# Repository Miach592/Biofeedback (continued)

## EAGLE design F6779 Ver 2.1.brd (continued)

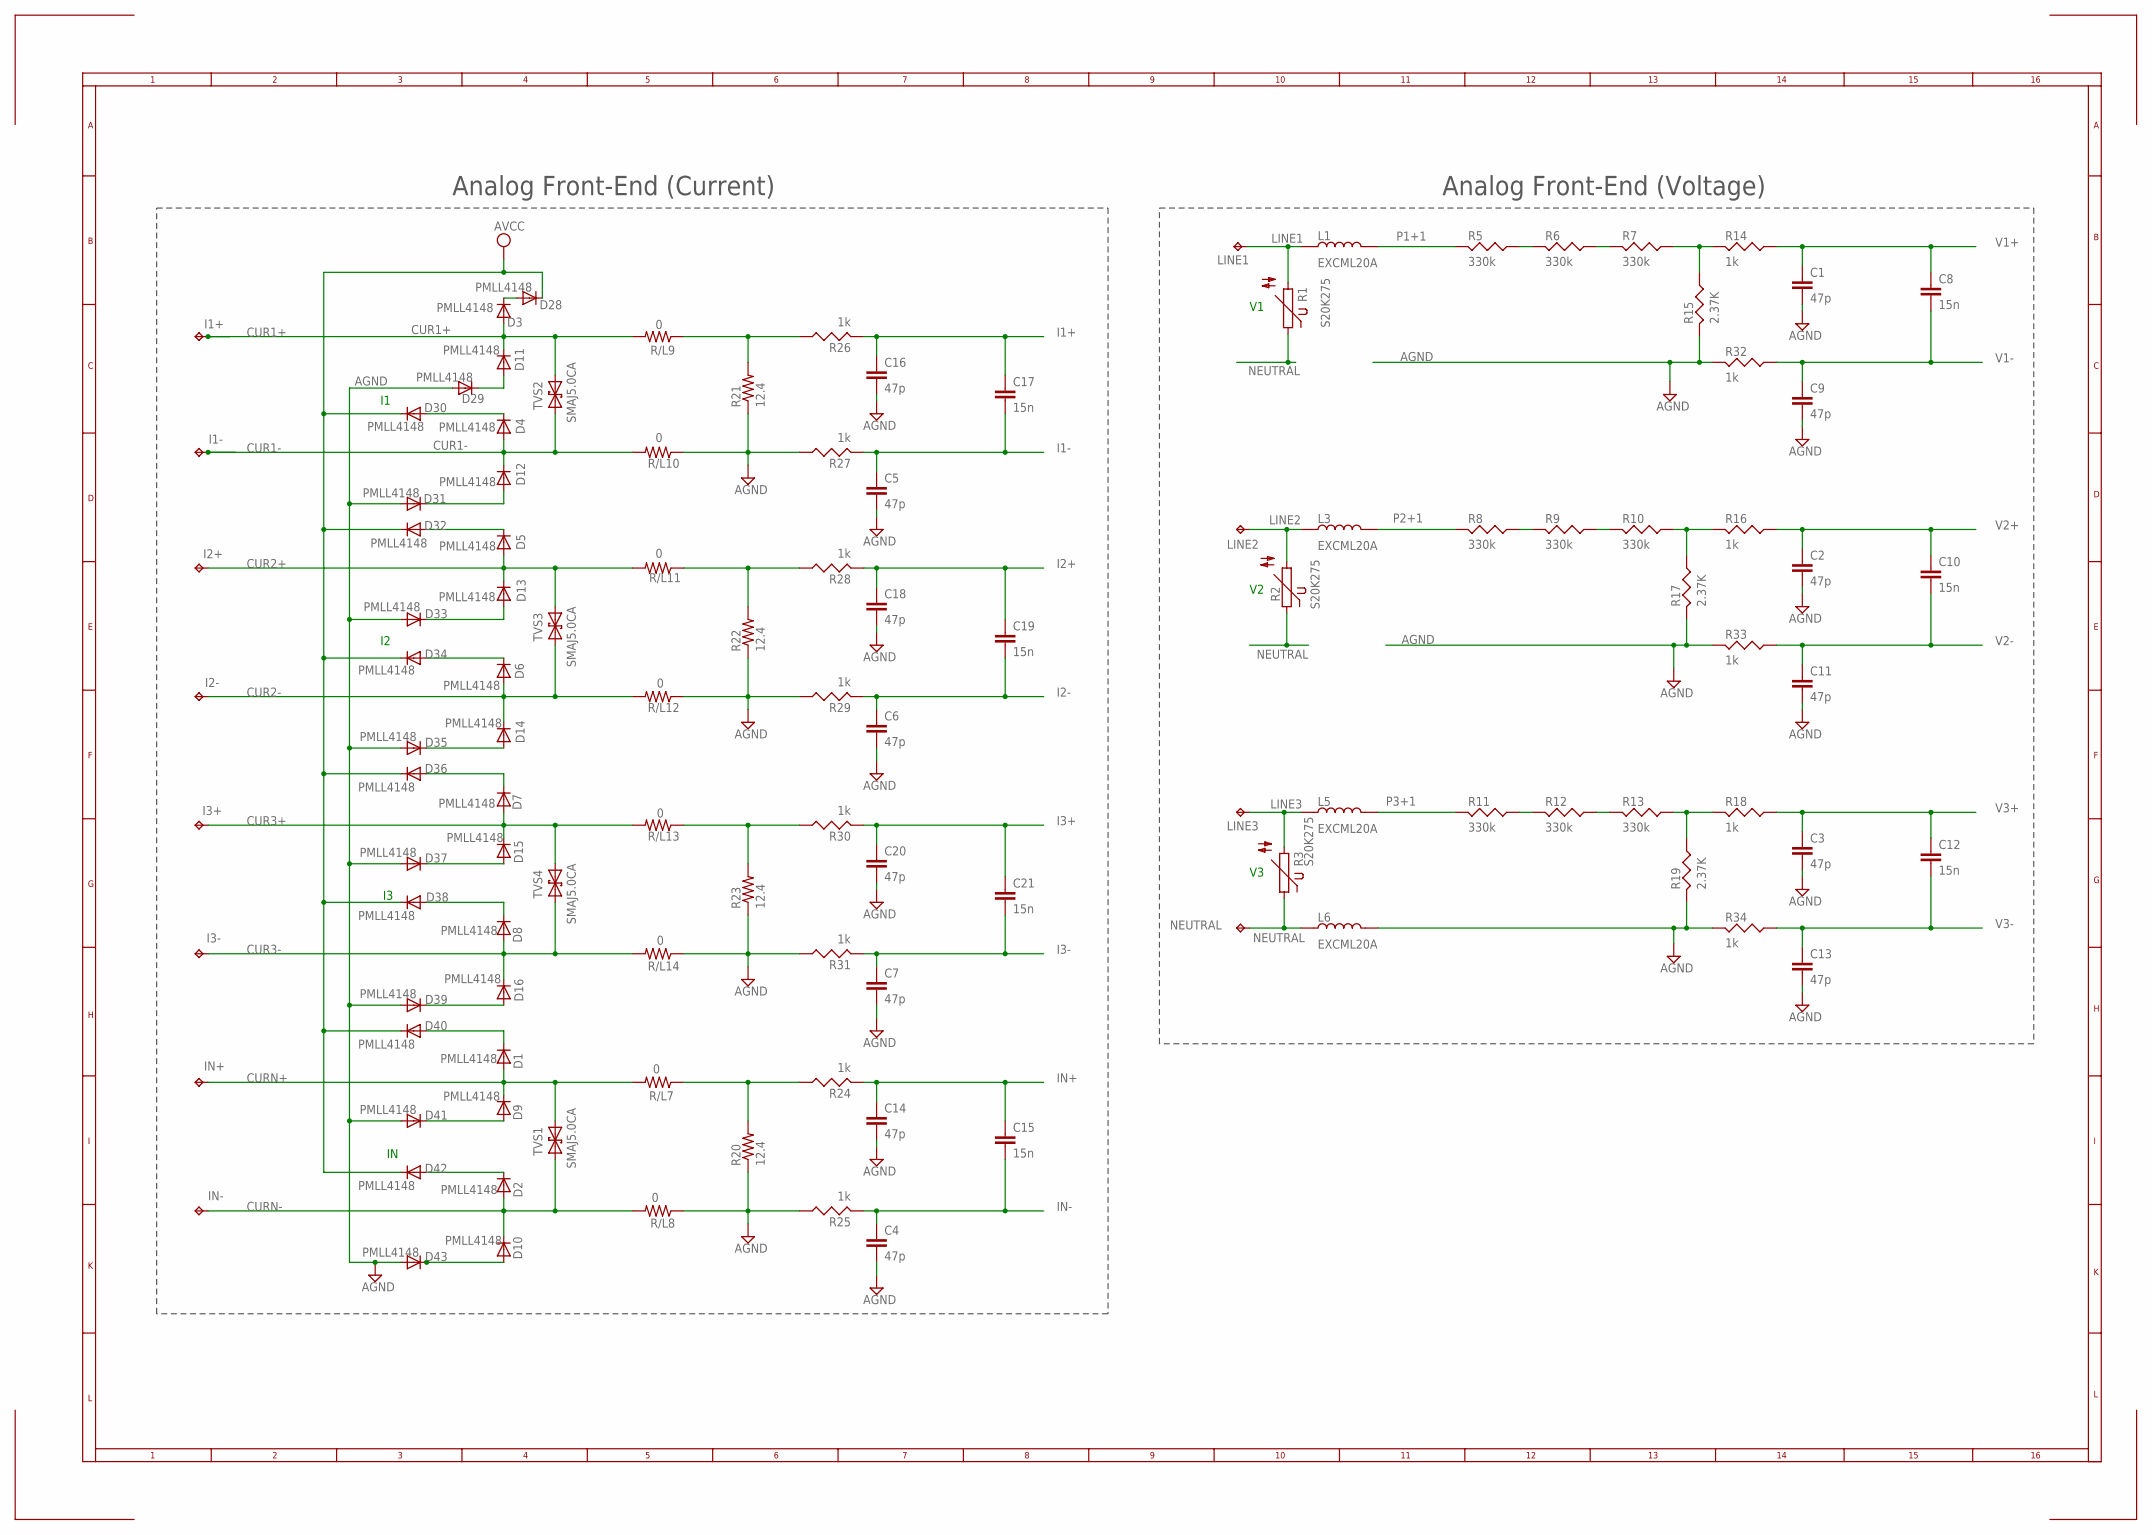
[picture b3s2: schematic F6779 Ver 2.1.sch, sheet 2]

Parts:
C1, C2, C3, C4, C5, C6, C7, C9, C11, C13, C14, C16, C18, C20: 47p; C0805
C8, C10, C12, C15, C17, C19, C21: 15n; C0805
D1, D2, D3, D4, D5, D6, D7, D8, D9, D10, D11, D12, D13, D14, D15, D16, D28, D29, D30, D31, D32, D33, D34, D35, D36, D37, D38, D39, D40, D41, D42, D43: PMLL4148; SOD80C
I1+, I1-, I2+, I2-, I3+, I3-: TPPAD1-20; P1-20
IN+: TPPAD1-20; P1-20
IN-: TPPAD1-20; P1-20
L1, L3, L5, L6: EXCML20A; R0805
LINE1, LINE2, LINE3: TPPAD1-20; P1-20
NEUTRAL: TPPAD1-20; P1-20
R1, R2, R3: S20K275
R5, R6, R7, R8, R9, R10, R11, R12, R13: 330k; R0805
R14, R16, R18, R24, R25, R26, R27, R28, R29, R30, R31, R32, R33, R34: 1k; R0805
R15, R17, R19: 2.37K; R0805
R20, R21, R22, R23: 12.4; R0805
R/L7, R/L8, R/L9, R/L10, R/L11, R/L12, R/L13, R/L14: 0; R0805
TVS1, TVS2, TVS3, TVS4: SMAJ5.0CA; DO214AC

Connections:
AGND: C1.2, C2.2, C3.2, C4.2, C5.2, C6.2, C7.2, C9.2, C11.2, C13.2, C14.2, C16.2, C18.2, C20.2, D29.A, D31.A, D33.A, D35.A, D37.A, D39.A, D41.A, D43.A, L6.2, R15.2, R17.2, R19.2, R20.1, R21.1, R22.1, R23.1, R25.1, R27.1, R29.1, R31.1, R32.2, R33.2, R34.2, R/L8.1, R/L10.1, R/L12.1, R/L14.1; also elsewhere on the board
AVCC: D28.C, D30.C, D32.C, D34.C, D36.C, D38.C, D40.C, D42.C; also elsewhere on the board
CUR1+: D3.A, D11.C, I1+.TP, R/L9.2, TVS2.C (K)
CUR1-: D4.A, D12.C, I1-.TP, R/L10.2, TVS2.A
CUR2+: D5.A, D13.C, I2+.TP, R/L11.2, TVS3.C (K)
CUR2-: D6.A, D14.C, I2-.TP, R/L12.2, TVS3.A
CUR3+: D7.A, D15.C, I3+.TP, R/L13.2, TVS4.C (K)
CUR3-: D8.A, D16.C, I3-.TP, R/L14.2, TVS4.A
CURN+: D1.A, D9.C, IN+.TP, R/L7.2, TVS1.C (K)
CURN-: D2.A, D10.C, IN-.TP, R/L8.2, TVS1.A
I1+: C16.1, C17.1, R26.2; also elsewhere on the board
I1-: C5.1, C17.2, R27.2; also elsewhere on the board
I2+: C18.1, C19.1, R28.2; also elsewhere on the board
I2-: C6.1, C19.2, R29.2; also elsewhere on the board
I3+: C20.1, C21.1, R30.2; also elsewhere on the board
I3-: C7.1, C21.2, R31.2; also elsewhere on the board
IN+: C14.1, C15.1, R24.2; also elsewhere on the board
IN-: C4.1, C15.2, R25.2; also elsewhere on the board
LINE1: L1.1, LINE1.TP, R1.2
LINE2: L3.1, LINE2.TP, R2.2
LINE3: L5.1, LINE3.TP, R3.2
unnamed: R20.2, R24.1, R/L7.1
unnamed: R5.1, R6.2
unnamed: R6.1, R7.2
unnamed: R7.1, R14.2, R15.1
unnamed: R8.1, R9.2
unnamed: R9.1, R10.2
unnamed: R10.1, R16.2, R17.1
unnamed: D3.C, D28.A
unnamed: D11.A, D29.C
unnamed: R23.2, R30.1, R/L13.1
unnamed: R11.1, R12.2
unnamed: R22.2, R28.1, R/L11.1
unnamed: R21.2, R26.1, R/L9.1
unnamed: R12.1, R13.2
unnamed: R13.1, R18.2, R19.1
unnamed: D4.C, D30.A
unnamed: D12.A, D31.C
unnamed: D5.C, D32.A
unnamed: D13.A, D33.C
unnamed: D6.C, D34.A
unnamed: D14.A, D35.C
unnamed: D7.C, D36.A
unnamed: D15.A, D37.C
unnamed: D8.C, D38.A
unnamed: D16.A, D39.C
unnamed: D1.C, D40.A
unnamed: D9.A, D41.C
unnamed: D2.C, D42.A
unnamed: D10.A, D43.C
NEUTRAL: L6.1, NEUTRAL.TP, R1.1, R2.1, R3.1; also elsewhere on the board
P1+1: L1.2, R5.2; also elsewhere on the board
P2+1: L3.2, R8.2; also elsewhere on the board
P3+1: L5.2, R11.2; also elsewhere on the board
V1+: C1.1, C8.1, R14.1; also elsewhere on the board
V1-: C8.2, C9.1, R32.1; also elsewhere on the board
V2+: C2.1, C10.1, R16.1; also elsewhere on the board
V2-: C10.2, C11.1, R33.1; also elsewhere on the board
V3+: C3.1, C12.1, R18.1; also elsewhere on the board
V3-: C12.2, C13.1, R34.1; also elsewhere on the board

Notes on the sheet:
Analog Front-End (Voltage)
Analog Front-End (Current)

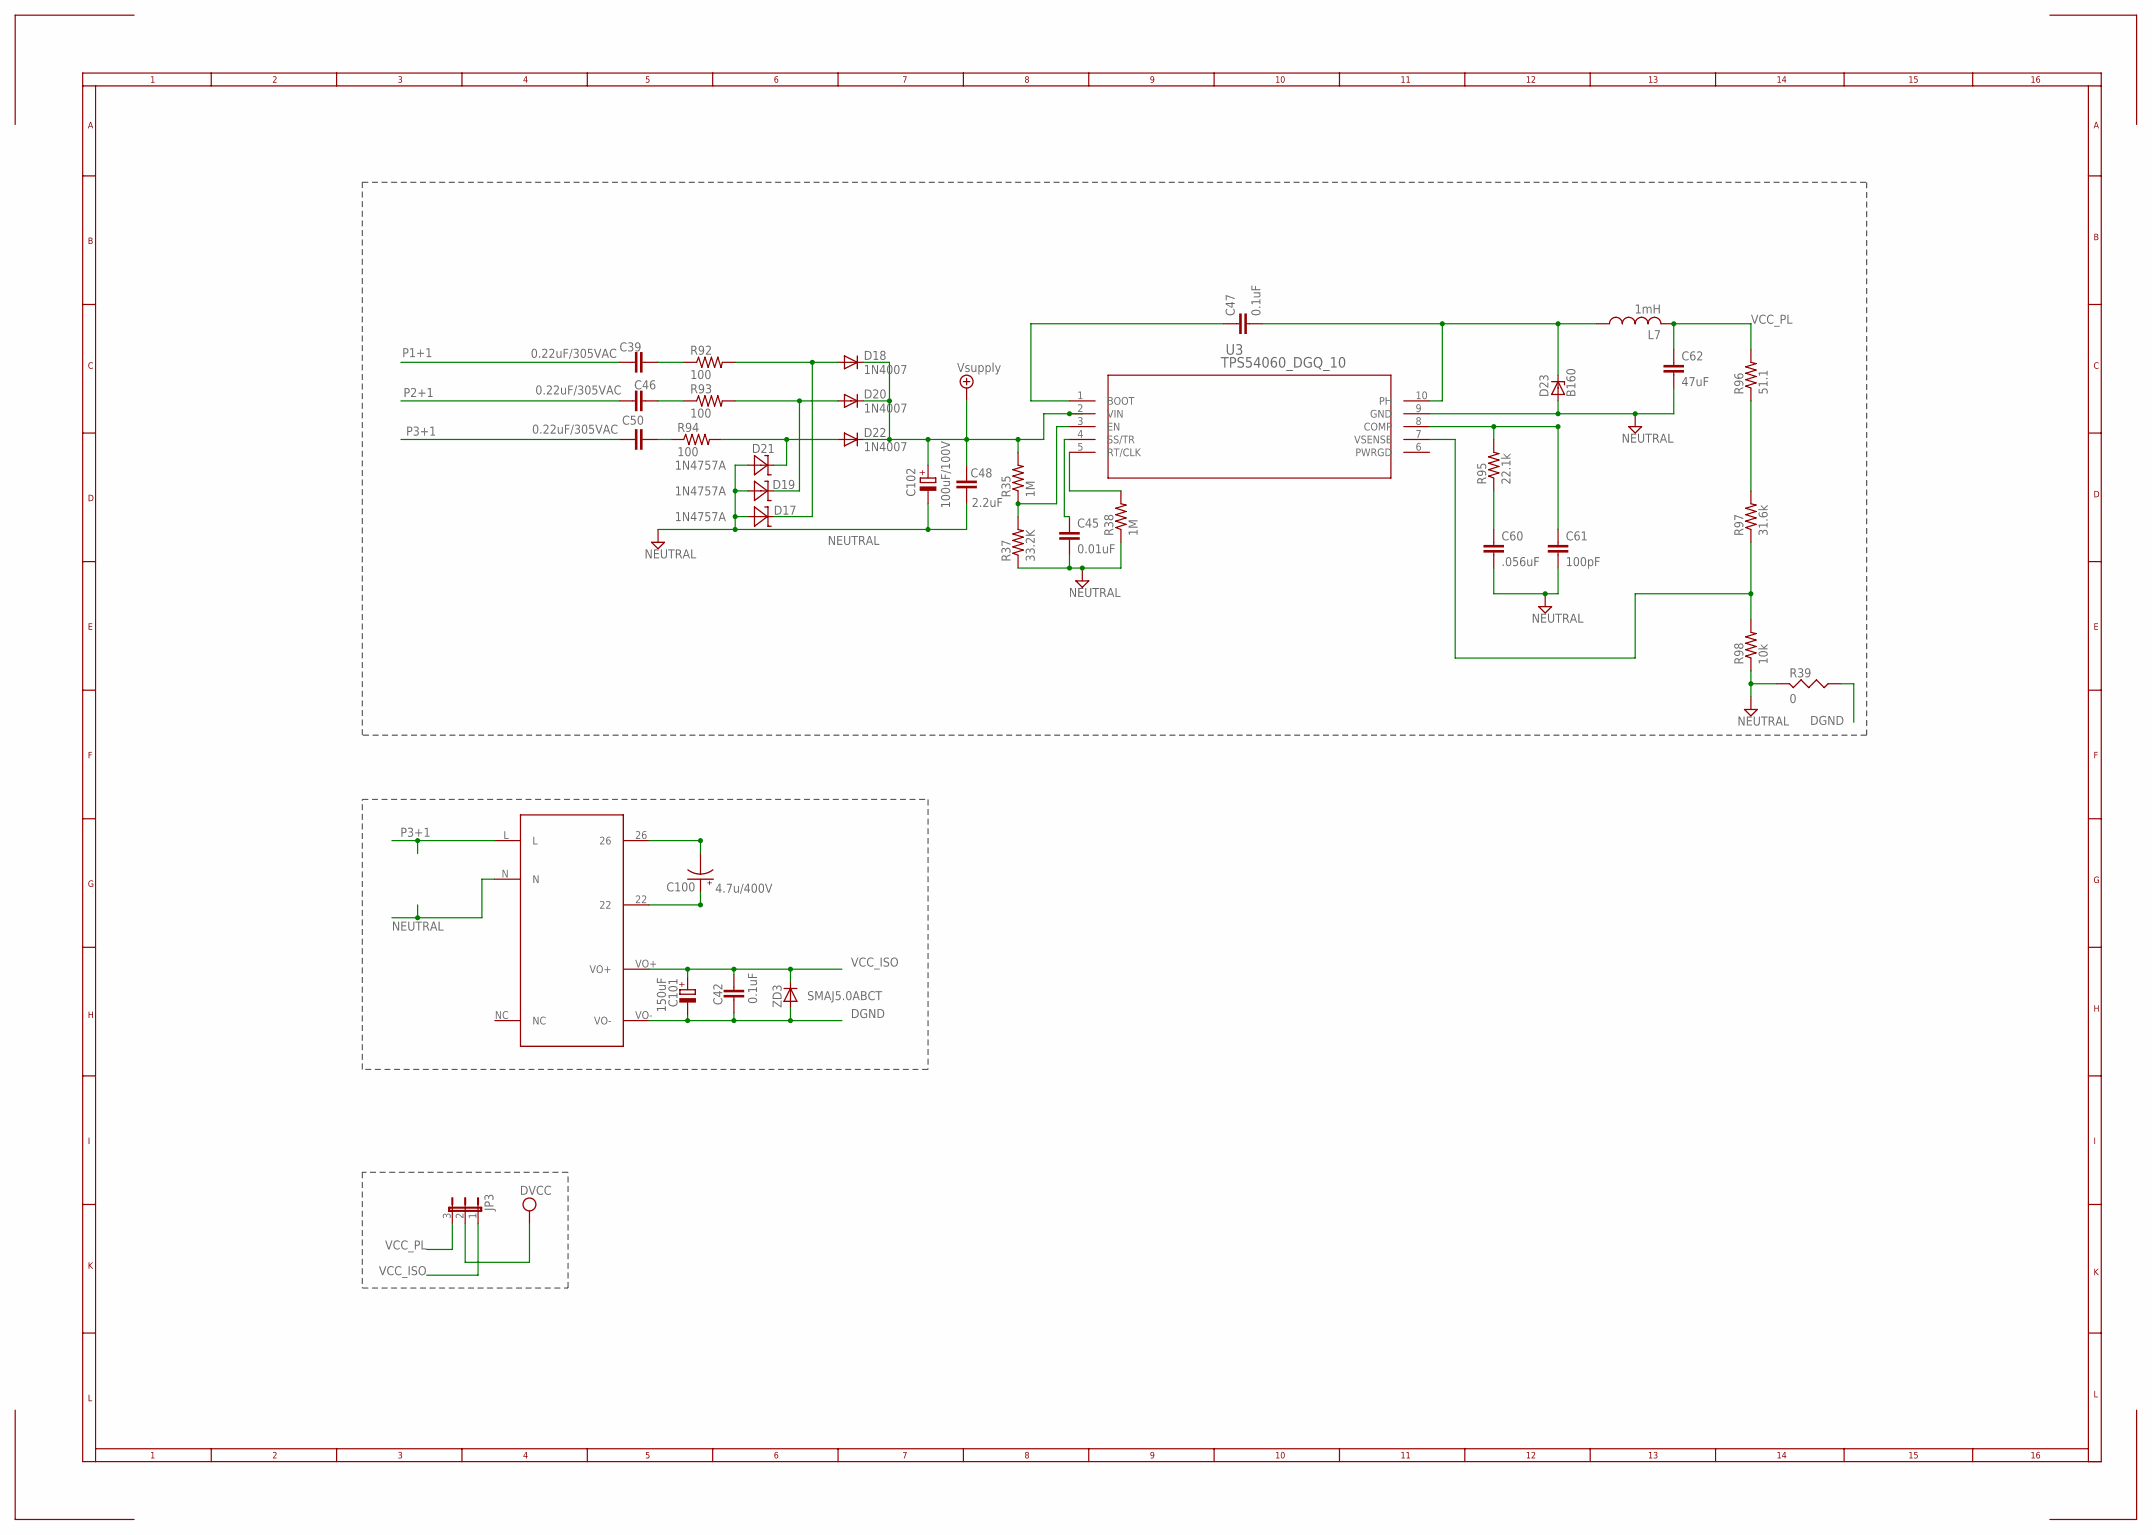
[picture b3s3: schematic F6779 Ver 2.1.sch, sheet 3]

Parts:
C39, C46, C50: 0.22uF/305VAC; C15B8
C42, C47: 0.1uF; C0603
C45: 0.01uF; C0603
C48: 2.2uF; C1210
C60: .056uF; C0603
C61: 100pF; C0603
C62: 47uF; C1210
C100: 4.7u/400V; E5-10,5
C101: 150uF; E2-5
C102: 100uF/100V; E5-10,5
D17, D19, D21: 1N4757A; DO41Z10
D18, D20, D22: 1N4007; DO41-10
D23: B160; SMB
JP3: JP2E; JP2
L7: 1mH; INDUCTOR_POWER_SUPPLY_6779
R35, R38: 1M; R0603
R37: 33.2K; R0603
R39: 0; R0805
R92, R93, R94: 100; 0414/15
R95: 22.1k; R0603
R96: 51.1; R0603
R97: 31.6k; R0603
R98: 10k; R0603
U3: TPS54060_DGQ_10; DGQ10_1P88X1P57
U$1: CUI_XR
ZD3: SMAJ5.0ABCT; DO214AC

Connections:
DGND: C42.2, C101.-, R39.1, U$1.VO-, ZD3.A; also elsewhere on the board
DVCC: JP3.2; also elsewhere on the board
unnamed: C100.-, U$1.26
unnamed: C100.+, U$1.22
unnamed: R38.2, U3.5 (RT/CLK)
unnamed: D17.C, D18.A, R92.2
unnamed: C45.1, U3.4 (SS/TR)
unnamed: R35.1, R37.2, U3.3 (EN)
unnamed: D19.C, D20.A, R93.2
unnamed: C47.1, U3.1 (BOOT)
unnamed: C47.2, D23.C, L7.1, U3.10 (PH)
unnamed: C60.1, R95.1
unnamed: C39.2, R92.1
unnamed: C46.2, R93.1
unnamed: C50.2, R94.1
unnamed: C61.1, R95.2, U3.8 (COMP)
unnamed: R96.1, R97.2
unnamed: D21.C, D22.A, R94.2
unnamed: R97.1, R98.2, U3.7 (VSENSE)
NEUTRAL: C45.2, C48.2, C60.2, C61.2, C62.2, C102.-, D17.A, D19.A, D21.A, D23.A, R37.1, R38.1, R39.2, R98.1, U3.9 (GND), U$1.N; also elsewhere on the board
P1+1: C39.1; also elsewhere on the board
P2+1: C46.1; also elsewhere on the board
P3+1: C50.1, U$1.L; also elsewhere on the board
VCC_ISO: C42.1, C101.+, JP3.1, U$1.VO+, ZD3.C
VCC_PL: C62.1, JP3.3, L7.2, R96.2
VSUPPLY: C48.1, C102.+, D18.C, D20.C, D22.C, R35.2, U3.2 (VIN); also elsewhere on the board

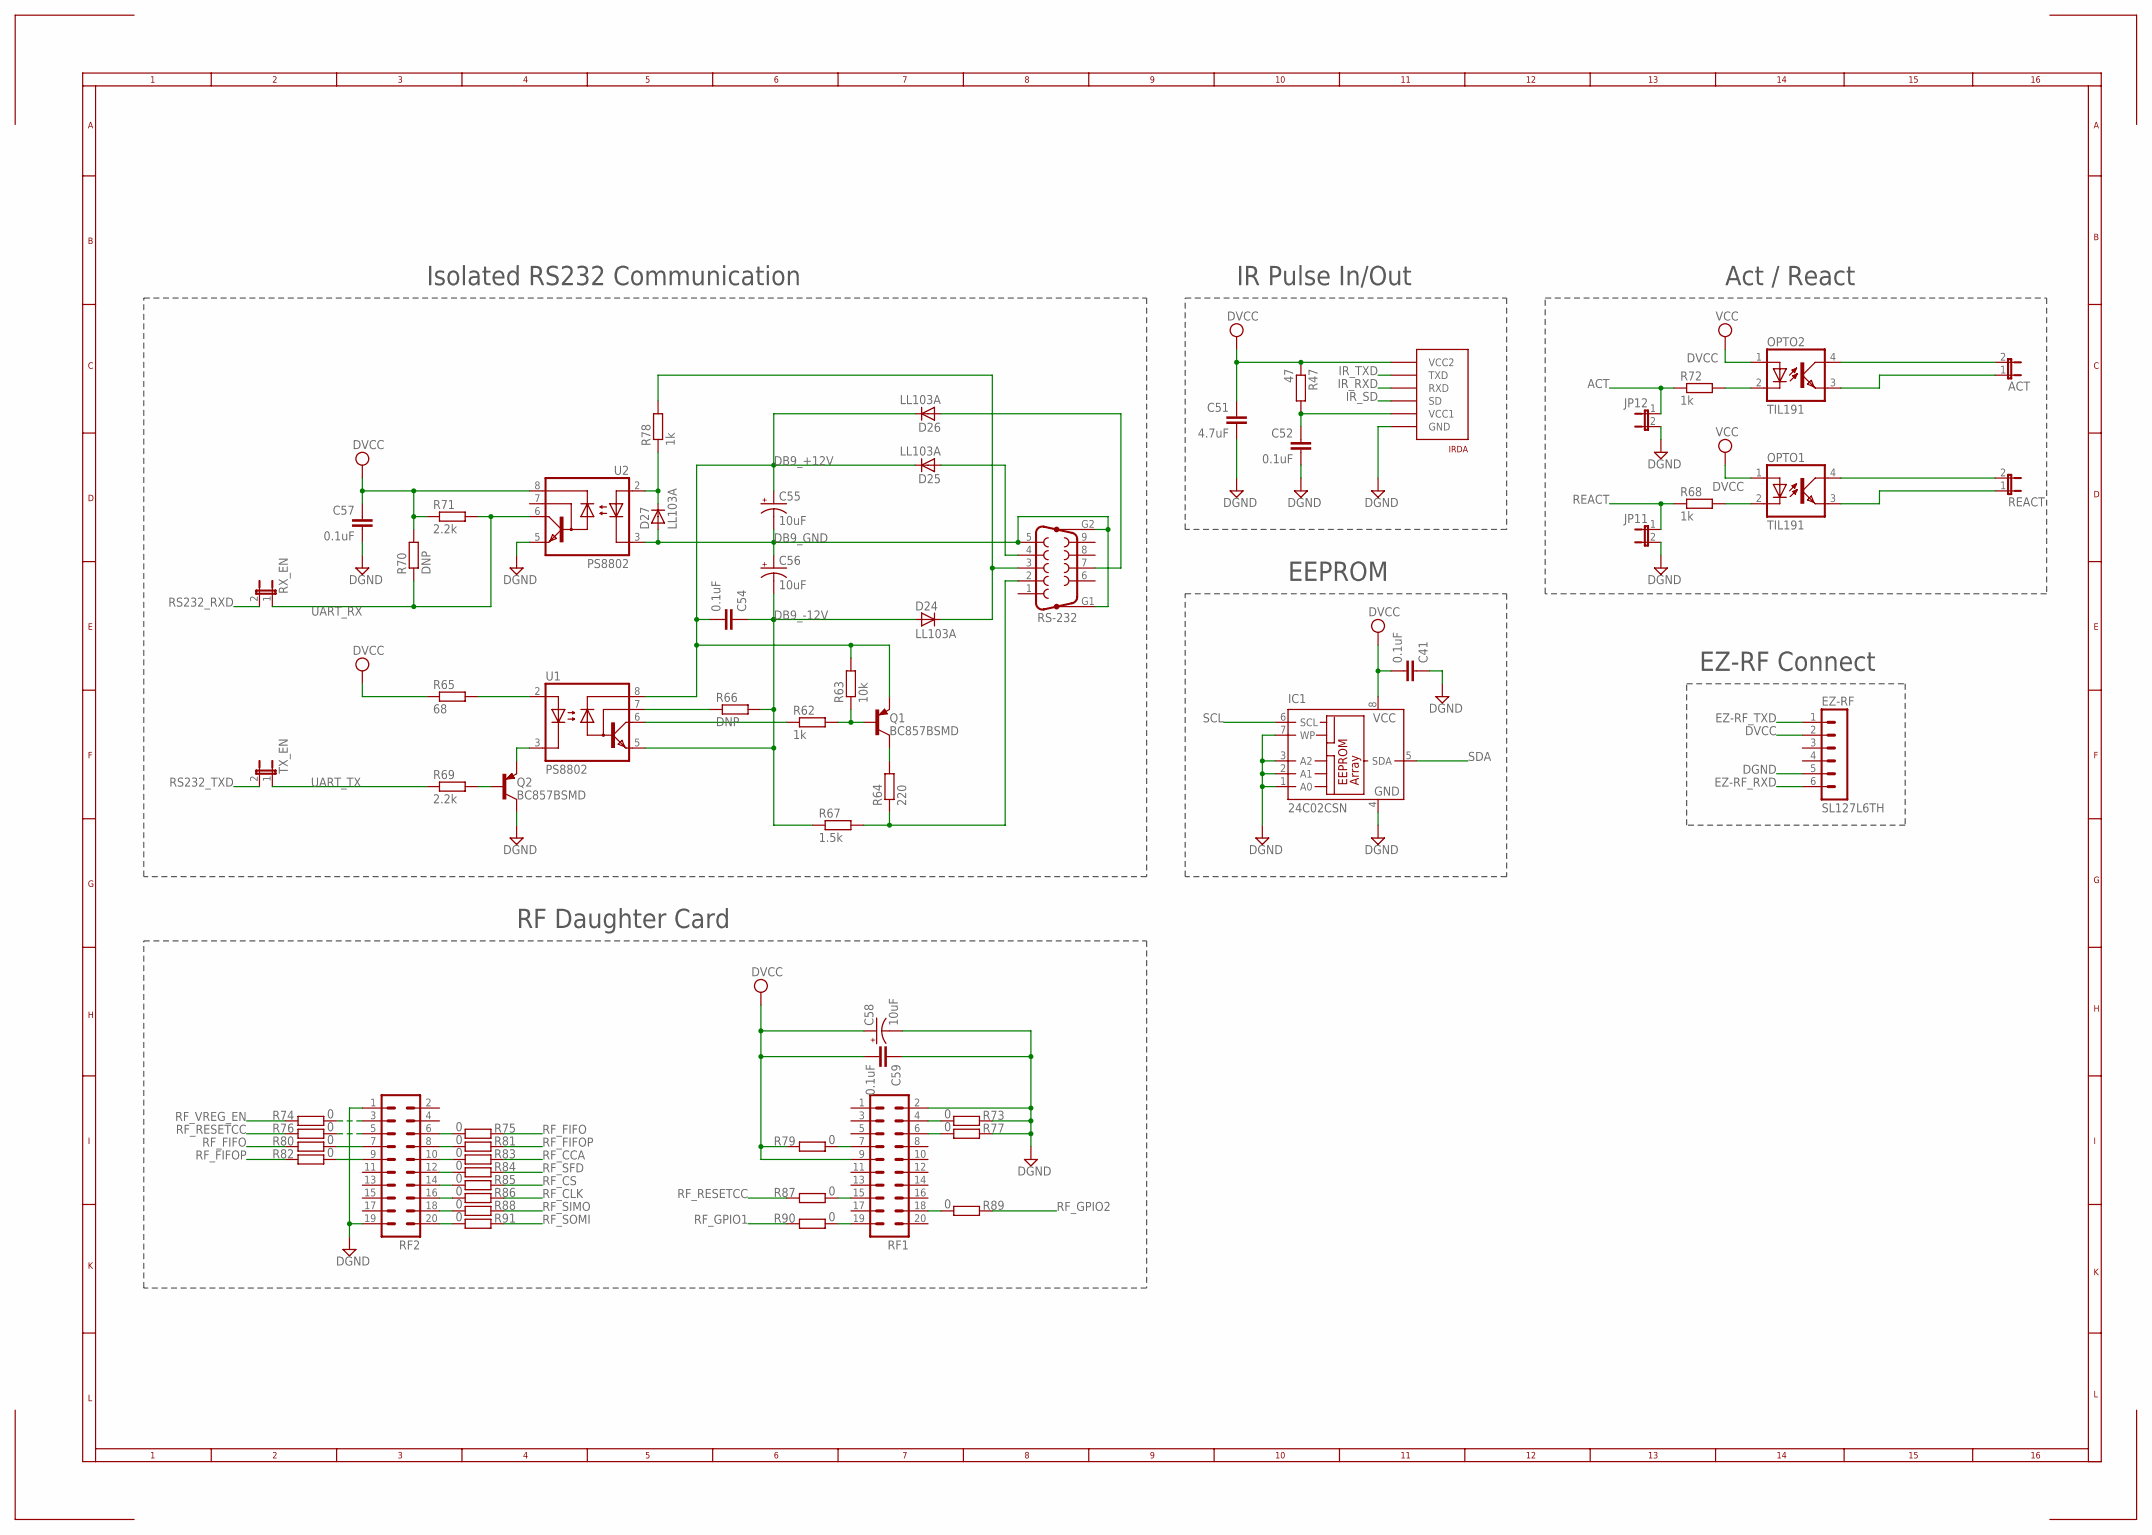
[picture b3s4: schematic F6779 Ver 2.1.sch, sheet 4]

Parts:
ACT: JP1E; JP1
C41, C52, C54, C57, C59: 0.1uF; C0603
C51: 4.7uF; C0603
C55, C56, C58: 10uF; CT3216
D24, D25, D26, D27: LL103A; SOD80
EZ-RF: SL127L6TH; SL127L6_MPE
IC1: 24C02CSN; SO-08
IRDA: TFBS4711-TT1; TFBS4711
JP11, JP12: JP1E; JP1
OPTO1, OPTO2: TIL191; DIL04
Q1, Q2: BC857BSMD; SOT23-BEC
R47: 47; R0603
R62, R68, R72, R78: 1k; R0603
R63: 10k; R0603
R64: 220; R0603
R65: 68; R0603
R66, R70: DNP; R0603
R67: 1.5k; R0603
R69, R71: 2.2k; R0603
R73, R74, R75, R76, R77, R79, R80, R81, R82, R83, R84, R85, R86, R87, R88, R89, R90, R91: 0; R0603
REACT: JP1E; JP1
RF1, RF2: TFM-110-02-SM-D-A-K
RS-232: F09VP
RX_EN: JP1E; JP1
TX_EN: JP1E; JP1
U1, U2: PS8802; SO08

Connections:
ACT: JP12.1, R72.1; also elsewhere on the board
DB9_+12V: C54.2, C55.+, D25.1 (C), D26.1 (C), Q1.E, R63.2, U1.8 (VCC)
DB9_-12V: C54.1, C56.-, D24.2 (A), R66.2, R67.1, U1.5 (GND)
DB9_GND: C55.-, C56.+, D27.2 (A), RS-232.5, RS-232.G1, RS-232.G2, U2.3 (C)
DGND: C41.1, C51.2, C52.2, C57.2, C58.-, C59.1, EZ-RF.5, IC1.1 (A0), IC1.2 (A1), IC1.3 (A2), IC1.4 (GND), IC1.7 (WP), IRDA.P$6 (GND), JP11.2, JP12.2, Q2.C, R73.2, R77.2, RF1.2, RF2.1, RF2.19, U2.5 (GND); also elsewhere on the board
DVCC: C41.2, C51.1, C57.1, C58.+, C59.2, EZ-RF.2, IC1.8 (VCC), IRDA.P$1 (VCC2), OPTO1.1 (A), OPTO2.1 (A), R47.1, R65.1, R70.2, R71.1, R79.1, RF1.9, U2.8 (VCC); also elsewhere on the board
EZ-RF_RXD: EZ-RF.6; also elsewhere on the board
EZ-RF_TXD: EZ-RF.1; also elsewhere on the board
IR_RXD: IRDA.P$3 (RXD); also elsewhere on the board
IR_SD: IRDA.P$4 (SD); also elsewhere on the board
IR_TXD: IRDA.P$2 (TXD); also elsewhere on the board
unnamed: ACT.2, OPTO2.4 (COL)
unnamed: R65.2, U1.2 (A)
unnamed: ACT.1, OPTO2.3 (EMIT)
unnamed: OPTO2.2 (C), R72.2
unnamed: Q2.B, R69.2
unnamed: R64.1, R67.2, RS-232.2
unnamed: R62.1, U1.6 (VO)
unnamed: Q1.B, R62.2, R63.1
unnamed: R74.2, RF2.3
unnamed: Q1.C, R64.2
unnamed: R66.1, U1.7 (VB)
unnamed: R76.2, RF2.5
unnamed: C52.1, IRDA.P$5 (VCC1), R47.2
unnamed: R79.2, RF1.7
unnamed: R73.1, RF1.4
unnamed: R87.2, RF1.15
unnamed: R77.1, RF1.6
unnamed: R83.1, RF2.10
unnamed: R84.1, RF2.12
unnamed: R85.1, RF2.14
unnamed: D27.1 (C), R78.1, U2.2 (A)
unnamed: R86.1, RF2.16
unnamed: R88.1, RF2.18
unnamed: R91.1, RF2.20
unnamed: OPTO1.4 (COL), REACT.2
unnamed: D24.1 (C), R78.2, RS-232.3
unnamed: OPTO1.3 (EMIT), REACT.1
unnamed: D26.2 (A), RS-232.7
unnamed: D25.2 (A), RS-232.4
unnamed: OPTO1.2 (C), R68.2
unnamed: Q2.E, U1.3 (C)
unnamed: R90.2, RF1.19
unnamed: R89.1, RF1.18
unnamed: R80.2, RF2.7
unnamed: R82.2, RF2.9
unnamed: R81.1, RF2.8
unnamed: R75.1, RF2.6
REACT: JP11.1, R68.1; also elsewhere on the board
RF_CCA: R83.2; also elsewhere on the board
RF_CLK: R86.2; also elsewhere on the board
RF_CS: R85.2; also elsewhere on the board
RF_FIFO: R75.2, R80.1; also elsewhere on the board
RF_FIFOP: R81.2, R82.1; also elsewhere on the board
RF_GPIO1: R90.1; also elsewhere on the board
RF_GPIO2: R89.2; also elsewhere on the board
RF_RESETCC: R76.1, R87.1; also elsewhere on the board
RF_SFD: R84.2; also elsewhere on the board
RF_SIMO: R88.2; also elsewhere on the board
RF_SOMI: R91.2; also elsewhere on the board
RF_VREG_EN: R74.1; also elsewhere on the board
RS232_RXD: RX_EN.2; also elsewhere on the board
RS232_TXD: TX_EN.2; also elsewhere on the board
SCL: IC1.6 (SCL); also elsewhere on the board
SDA: IC1.5 (SDA); also elsewhere on the board
UART_RX: R70.1, R71.2, RX_EN.1, U2.6 (VO)
UART_TX: R69.1, TX_EN.1

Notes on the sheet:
RF Daughter Card
IR Pulse In/Out
Isolated RS232 Communication
EZ-RF Connect
Act / React
EEPROM

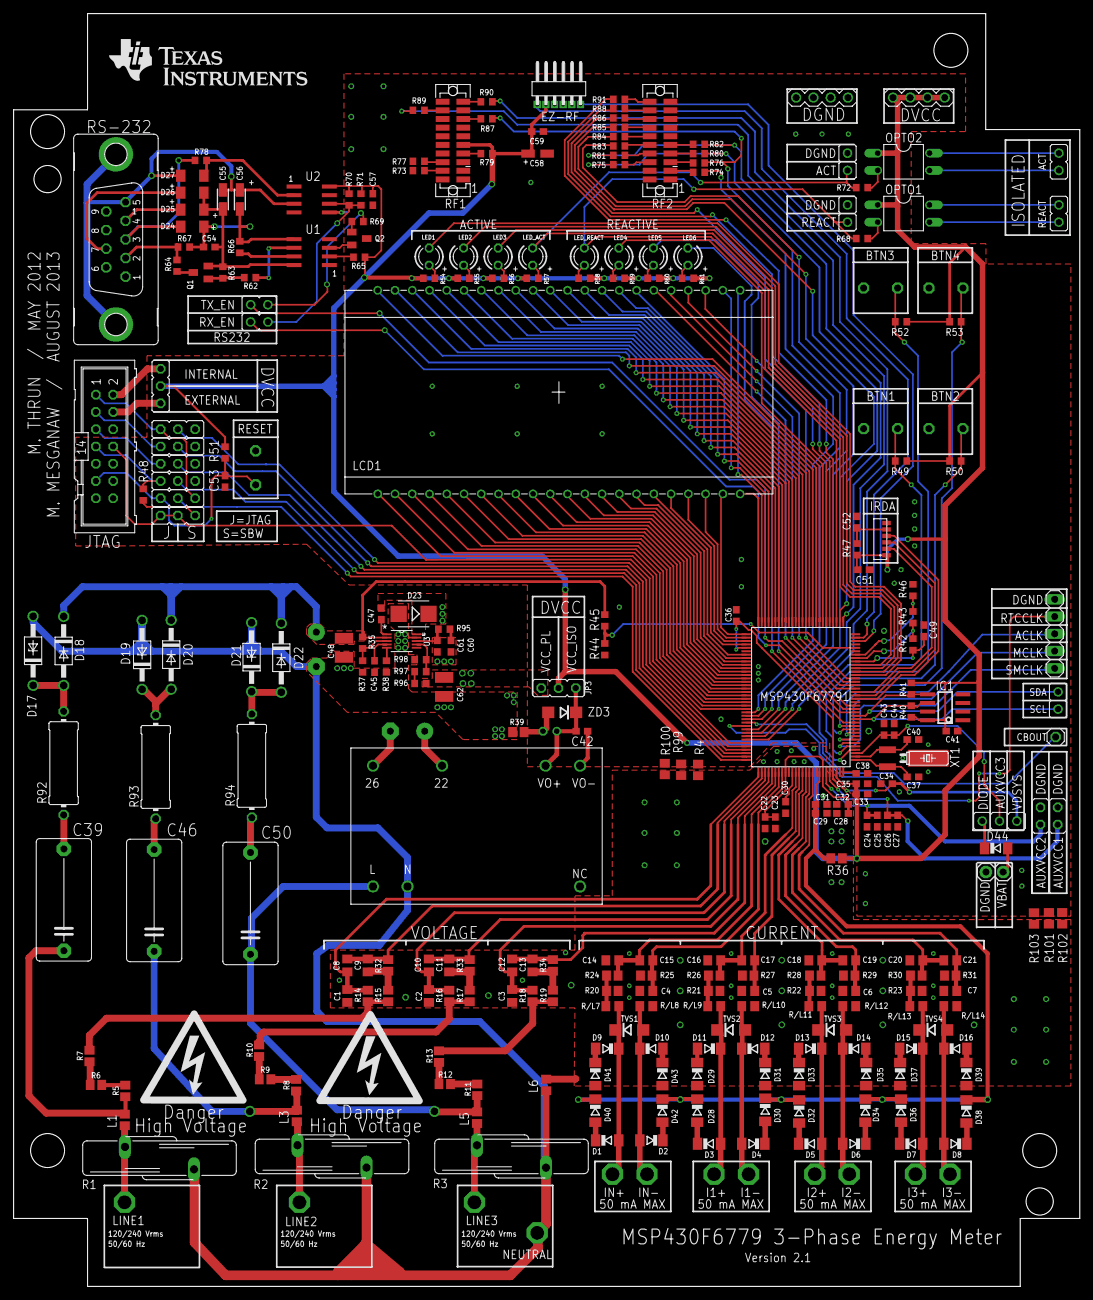
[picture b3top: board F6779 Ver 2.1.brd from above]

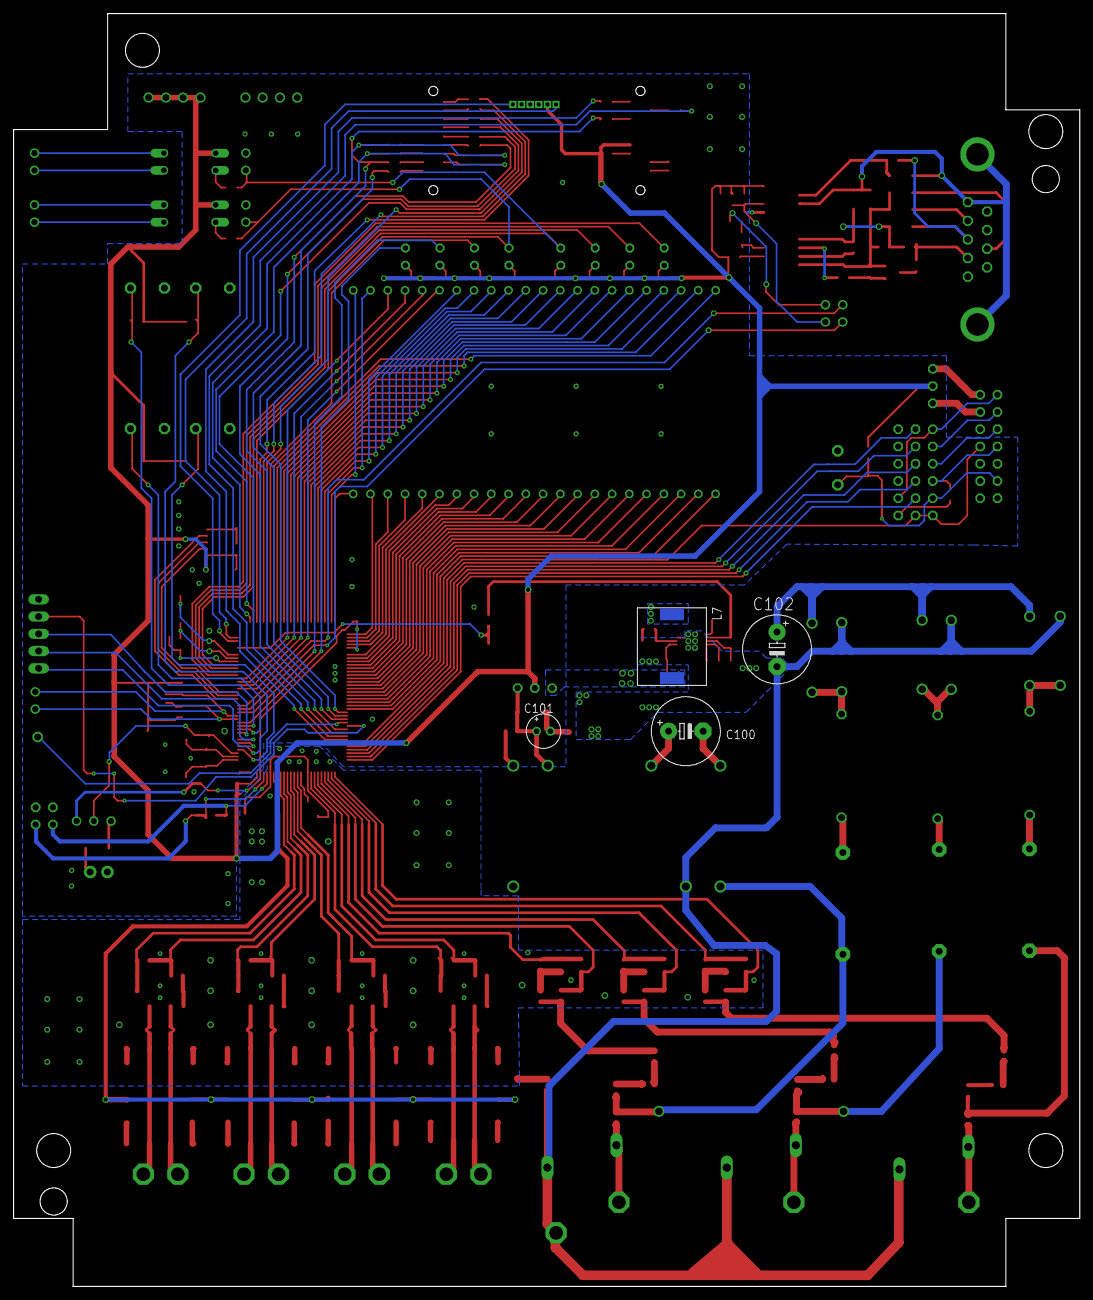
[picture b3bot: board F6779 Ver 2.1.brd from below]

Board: 2 copper layers, 156.9 x 187.4 mm, 295 parts (4 on the bottom side), 243 nets.

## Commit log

2019-04-19 Backlink to CADLAB.io has been added.
2019-04-19 Adding a couple of files to the master
2019-04-19 Filterstufe ohne Schutzeinrichtungen und ohne Spannungsversorgung
2019-04-19 Kann ignoriert werden
2019-04-19 Was tue ich hier?
2019-04-19 Noch ein Test
2019-04-23 Erweiterungen am Schaltplan
2019-04-29 Nächste Erweiterung
2019-04-30 Nächste Bearbeitung
2019-05-01 Add files via upload
    Initial Release!
    Release Notes:
    - capasitors for power supply at msp430 still missing
    - RGB LED is missing
    - dealing with open pins must be clarified
2019-05-01 Überspannungsschutz hinzugefügt
2019-05-01 just in case...
2019-05-02 Add files via upload
    Einmal auwischen bitte in Gang 4!
2019-05-02 Simulationfiles
2019-05-03 Testpunkte, Widerstand hinter Poti, zusätzlich noch Power Supply Platine
2019-05-04 Schönheitsanpassungen
2019-05-09 Pinout erweitert, Analog u. digital Power Caps, Taster, LEDs
2019-05-09 Fragen aktualisiert
2019-05-10 Antworten fuer Digitalteil addiert
2019-05-12 Initial version of analog and digital design
2019-05-14 Libraries
2019-05-14 Schraubklemmen-Libs
2019-05-14 Analoges Layout_Teil1
2019-05-15 Zweite Layout-Sitzung
2019-05-16 Analog-Layout final, nur noch Schönheits-OPs fällig
2019-05-16 Bauteile des Digital-Teils auf dem Board platziert
2019-05-18 next version of digital part implementation
2019-05-19 first version of analog & digital part completed --> ready for review
2019-05-19 modified version of analog & digital part complete
2019-05-21 Analoger Teil, Klappe die Zweite.
2019-05-22 next Version of layout 2.0: - changed position of leds, buttons and jtag connector - not every pin is routed to a connector pin - AGND,DGND on top and bottom
2019-05-22 some improvements. - DVCC lines extended
2019-05-22 Last changes of Version 2
2019-05-23 Vias und Entfernungen erhöhen
2019-05-25 Moved signals so GND can surround the low amplitude signals
2019-05-28 Outlines hinzugefügt
2019-05-29 Buttom joints shortened, Labeling added
2019-05-29 Abstand erhöht bei einem Bauteil
2019-05-29 Signature and further changes
2019-05-29 rotated a pinout-connector
2019-05-29 moved gnd and added more gnd vias
2019-05-29 Necessary input for the ordering @ pcb-pool
2019-05-31 moved some wires for more GND-shielding, added labeling
2019-05-31 final changes
2019-05-31 moved some analog signals, added shielding, two parts on lower ina need to be moved
2019-05-31 AGND & AVCC
2019-05-31 Schönheitsoperation
2019-06-01 buttons replaced, addad some labeling
2019-06-01 few small details
2019-06-01 Release Version
2019-06-02 Bestell-Liste Reichelt
2019-06-02 Power supply, release version
2019-06-04 Bestellliste Farnell
2019-06-05 Release Version tagged and removed old version
2019-06-05 Libs and Sim added Revision removed
2019-06-08 Logos added
2019-06-18 Fixed 3 buttons Added UART as back-channel to JTAG header acc. http://www.ti.com/lit/ug/slau647m/slau647m.pdf p.19
